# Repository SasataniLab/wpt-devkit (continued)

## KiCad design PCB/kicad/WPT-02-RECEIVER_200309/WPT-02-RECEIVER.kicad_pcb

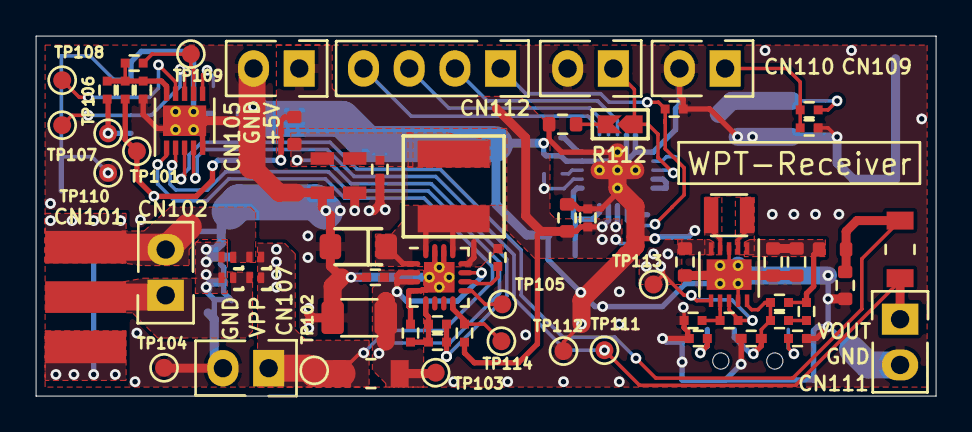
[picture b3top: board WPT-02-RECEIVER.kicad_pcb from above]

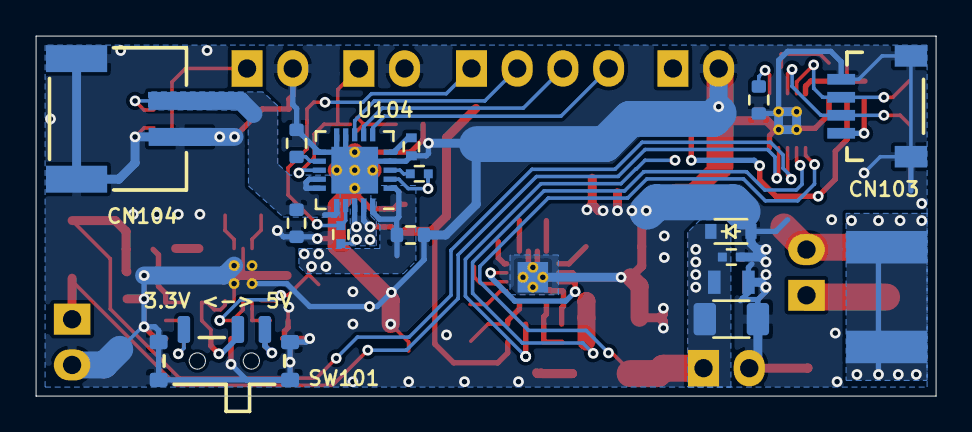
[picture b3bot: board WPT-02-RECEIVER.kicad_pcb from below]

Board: 4 copper layers, 50.0 x 20.0 mm, 84 parts (15 on the bottom side), 40 nets.

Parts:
C101: 0.022u/50(X7R); GRM15
C102, C107: 10u/50(X5R); GRM31
C103, C104, C116, C119: 0.1u/50(X7R); GRM15
C105: 1000p/50(C0G); GRM15
C106: 0.1u/100(X7R); GRM21
C108, C109: 22u/16(X5R); GRM21
C110: 10n/50(X7R); GRM15
C111: 10u/25(X5R); GRM18
C112, C122: 22u/10(X5R); GRM18
C113: 68p/50(C0G); GRM15
C117, C118, C120: 4.7u/16(X5R); GRM18
C123: OPEN; GRM18
CN101: CON-SMA-EDGE-S
CN102, CN105, CN107, CN109, CN110, CN111: ULO-PH409-1*2SF11; ULO-PH409-1x2SX1
CN103: SM04B-SRSS-TB(LF)(SN); SM04B-SRSS-TB
CN104: S2B-PH-SM4-TB(LF)(SN); S2B-PH-SM4-TB
CN112: ULO-PH409-1*4SF11; ULO-PH409-1x4SX1
D101, D102, D105, D106: PMEG6010AESBYL; SOD-993_Nexperia
D103: S210FA; SOD-123FA_OnSemi
D104: MM3Z39VT1G; SOD-323
FB101, FB102: BLM18PG330SN1D; BLM18
L101: NR5040T4R7N; NR5040
L102: DFE252012P-3R3M=P2; DFE252012C
R101: 82kF; R_0402
R102: 18kF; R_0402
R103, R107: 27mF(1/4W); R_1206
R104, R116: 10kF; R_0402
R105, R106, R108, R114, R119: OPEN; R_0402
R109: 750kF; R_0402
R110: 91kF; R_0402
R111: 820kF; R_0402
R112: SHORT_JUMPER; JP_SMD
R113, R115: 0; R_0402
R117: 0; R_0603
R118: NCP15XH103F03RC; NTC_0402
R120, R126: 100kF; R_0402
R121: 143kF; R_0402
R123: 100kF; R_0603
R124: 10kF; R_0603
SW101: CUS-12TB
TP101, TP102, TP103, TP104, TP105, TP106, TP107, TP108, TP109, TP110, TP111, TP112, TP113, TP114: TP1.0; TP_1mm
U101: TS30042-M000QFNR; QFN-16-1EP_3x3mm_Pitch0.5mm_Semtech
U102: MP2155GQ-Z; DFN-10-1EP_3x3mm_Pitch0.5mm_MPS
U103: PAC1720-1-AIA-TR; DFN-10-1EP_3x3mm_Pitch0.5mm_microchip_9Q
U104: MCP73871T-1CCI_ML; QFN-20-1EP_4x4mm_Pitch0.5mm_microchip_ML
VD101: CG0402MLC-3.3LG; CG0402

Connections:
+5V: C118.1, C119.1, CN105.1, FB101.2, R104.2, R114.2, R119.2, R120.2, TP101.1, U104.2, U104.18, U104.19
/CHG_EN: CN112.1, R119.1, R126.2, U104.17
/CHG_STAT1: CN112.2, U104.8
/CHG_STAT2: CN112.3, U104.7
/PWRGD_5V: R104.1, TP114.1, U101.8
/SCL: CN103.3, TP108.1, U103.9
/SDA: CN103.2, TP107.1, U103.8
/VEXT: CN103.1, R115.1, TP106.1
/VOUT: CN111.1, R107.1, TP111.1, U103.4
/~ALERT: R116.1, TP109.1, U103.7
/~CHG_PG: CN112.4, U104.6
GND: C102.2, C103.2, C104.2, C105.2, C106.2, C107.2, C108.2, C109.2, C111.2, C112.2, C116.2, C117.2, C118.2, C119.2, C120.2, C122.2, C123.2, CN103.4, CN103.FG, CN104.2, CN104.FG, CN105.2, CN107.2, CN109.2, CN110.2, CN111.2, D103.2, D104.2, D105.2, D106.2, R102.1, R106.1, R110.1, R113.1, R117.1, R118.1, R121.1, R123.1, R124.1, R126.1, SW101.FG, TP104.1, TP110.1, TP112.1, U101.4, U101.14, U101.15, U101.17, U102.3, U102.9, U102.11, U103.5, U103.11, U104.4, U104.9, U104.10, U104.11, U104.21, VD101.1
unnamed: C101.1, U101.10
unnamed: C101.2, D103.1, L101.1, U101.1, U101.12, U101.13, U101.16
unnamed: C102.1, C103.1, R103.1, TP103.1, U101.2, U101.3, U101.11, U103.2
unnamed: C104.1, C108.1, C109.1, C110.1, FB101.1, L101.2, R101.2
unnamed: C110.2, R101.1, R102.2, U101.5
unnamed: C112.1, C122.1, FB102.1, R109.2, R111.2, U102.1
unnamed: C113.1, R109.1
unnamed: C113.2, R111.1, SW101.2, U102.10, VD101.2
unnamed: C116.1, R114.1, R115.2, R116.2, U103.10
unnamed: C120.1, CN104.1, R105.2, U104.14, U104.15, U104.16
unnamed: C123.1, FB102.2, R107.2, U103.3
unnamed: CN101.1, CN102.1, D101.2, D105.1
unnamed: CN101.2, CN102.2, D102.2, D106.1
unnamed: CN109.1, R105.1, R106.2
unnamed: CN110.1, R112.2, U104.13
unnamed: L102.1, U102.4
unnamed: L102.2, U102.2
unnamed: R108.1, R113.2, U102.7
unnamed: R110.2, SW101.3
unnamed: R112.1, R124.2
unnamed: R117.2, U103.6
unnamed: R118.2, U104.5
unnamed: R120.1, U104.3
unnamed: R121.2, SW101.1
unnamed: R123.2, U104.12
unnamed: TP105.1, U101.9
VCC: C111.1, C117.1, R108.2, TP113.1, U102.5, U102.6, U102.8, U104.1, U104.20
VPP: C105.1, C106.1, C107.1, CN107.1, D101.1, D102.1, D104.1, R103.2, TP102.1, U103.1

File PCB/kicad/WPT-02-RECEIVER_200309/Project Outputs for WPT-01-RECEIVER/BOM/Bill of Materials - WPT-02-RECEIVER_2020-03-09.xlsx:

Source: | E:\Dropbox\dev\prj\commissioned\University of Tokyo\WPT\electric\kicad\WPT-02-R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
Date: | 09/03/2020 07:57:30
Tool: | Eeschema (5.1.5)-3
Generator: | E:\Dropbox\dev\prj\kicad-library/bom_csv_grouped_by_value_with_fp.py
Component Count: | 84
Mount | Comment | Description | Designator | Footprint | Manufacturer | Manufacturer Part Number | Qnty | Qty for 25Units | Retailer
Yes | 0.022u/50(X7R) | CAP CER 0.022UF 50V X7R 0402 | C101, | murata:GRM15 | Murata Electronics | GRM155R71H223KA12D | 1 | 25
Yes | 10u/50(X5R) | CAP CER 10UF 50V X5R 1206 | C102, C107, | murata:GRM31 | Samsung Electro-Mechanics | CL31A106KBHNNNE | 2 | 50
Yes | 0.1u/50(X7R) | CAP CER 0.1UF 50V X7R 0402 | C103, C104, C116, C119, | murata:GRM15 | Murata Electronics | GCM155R71H104KE02D | 4 | 100
Yes | 1000p/50(C0G) | CAP CER 1000PF 50V 5% NP0 0402 | C105, | murata:GRM15 | Murata Electronics | GRM1555C1H102JA01D | 1 | 25
Yes | 0.1u/100(X7R) | CAP CER 0.1UF 100V X7R 0805 | C106, | murata:GRM21 | Murata Electronics | GCM21BR72A104KA37L | 1 | 25
Yes | 22u/16(X5R) | CAP CER 22UF 16V X5R 0805 | C108, C109, | murata:GRM21 | Samsung Electro-Mechanics | CL21A226MOCLRNC | 2 | 50
Yes | 10n/50(X7R) | CAP CER 10000PF 50V X7R 0402 | C110, | murata:GRM15 | Yageo | CC0402KRX7R9BB103 | 1 | 25
Yes | 10u/25(X5R) | CAP CER 10UF 25V 20% X5R 0603 | C111, | murata:GRM18 | Murata Electronics | GRM188R61E106MA73D | 1 | 25
Yes | 22u/10(X5R) | CAP CER 22UF 10V X5R 0603 | C112, C122, | murata:GRM18 | Murata Electronics | GRM188R61A226ME15D | 2 | 50
Yes | 68p/50(C0G) | CAP CER 68PF 50V C0G/NP0 0402 | C113, | murata:GRM15 | Murata Electronics | GCM1555C1H680JA16D | 1 | 25
Yes | 4.7u/16(X5R) | CAP CER 4.7UF 16V X5R 0603 | C117, C118, C120, | murata:GRM18 | Murata Electronics | GRM188R61C475KAAJD | 3 | 75
No | OPEN |  | C123, | murata:GRM18 |  |  | 1 | 25
No | CON-SMA-EDGE-S | CONN SMA JACK STR EDGE MNT | CN101, | RF_Solutions:CON-SMA-EDGE-S | RF Solutions | CON-SMA-EDGE-S | 1 | 25
No | ULO-PH409-1*2SF11 | CON HEADER 2 PIN THROUGHTHOLE 6.1/2.5/3mm HEIGHT | CN102, CN105, CN107, CN109, CN110, CN111, | ulo:ULO-PH409-1x2SX1 | ULO Electronic | ULO-PH409-1x2SX1 | 6 | 150
Yes | SM04B-SRSS-TB(LF)(SN) | CONN HEADER SH 4POS SIDE 1MM TIN | CN103, | Connectors_JST:SM04B-SRSS-TB | JST | SM04B-SRSS-TB(LF)(SN) | 1 | 25
Yes | S2B-PH-SM4-TB(LF)(SN) | CONN HEADER PH SIDE 2POS 2MM SMD | CN104, | Connectors_JST:S2B-PH-SM4-TB | JST | S2B-PH-SM4-TB(LF)(SN) | 1 | 25
No | ULO-PH409-1*4SF11 | CON HEADER 4 PIN THROUGHTHOLE 6.1/2.5/3mm HEIGHT | CN112, | ulo:ULO-PH409-1x4SX1 | ULO Electric | ULO-PH409-1*4SF11 | 1 | 25
Yes | PMEG6010AESBYL | DIODE SCHOTTKY 60V 1A DSN1006-2 | D101, D102, D105, D106, | Diodes_SMD:SOD-993_Nexperia | Nexperia | PMEG6010AESBYL | 4 | 100
Yes | S210FA | DIODE SCHOTTKY 100V 2A SOD123FA | D103, | Diodes_SMD:SOD-123FA_OnSemi | ON Semiconductor | S210FA | 1 | 25
Yes | MM3Z39VT1G | DIODE ZENER 39V 300MW SOD323 | D104, | Diodes_SMD:SOD-323 | ON Semiconductor | MM3Z39VT1G | 1 | 25
Yes | BLM18PG330SN1D | FERRITE CHIP 33 OHM 3000MA 0603 | FB101, FB102, | murata:BLM18 | Murata Electronics | BLM18PG330SN1D | 2 | 50
Yes | NR5040T4R7N | FIXED IND 4.7UH 3.1A 37.7 MOHM | L101, | taiyo-yuden:NR5040 | Taiyo Yuden | NR5040T4R7N | 1 | 25
Yes | DFE252012P-3R3M=P2 | FIXED IND 3.3UH 2.3A 140 MOHM | L102, | murata:DFE252012C | Murata Electronics | DFE252012P | 1 | 25
Yes | 82kF | RES SMD 82K OHM 1% 1/16W 0402 | R101, | yageo:R_0402 | Yageo | RC0402FR-0782KL | 1 | 25
Yes | 18kF | RES SMD 18K OHM 5% 1/16W 0402 | R102, | yageo:R_0402 | Yageo | RC0402FR-0718KL | 1 | 25
Yes | 27mF(1/4W) | RES 0.027 OHM 1% 1/4W 1206 3216Metric | R103, R107, | yageo:R_1206 | Yageo | RL1206FR-070R027L | 2 | 50
Yes | 10kF | RES SMD 10K OHM 1% 1/16W 0402 | R104, R116, | yageo:R_0402 | Yageo | RC0402FR-0710KL | 2 | 50
No | OPEN |  | R105, R106, R108, R114, R119, | yageo:R_0402 |  |  | 5 | 125
Yes | 750kF | RES SMD 750K OHM 1% 1/16W 0402 | R109, | yageo:R_0402 | Yageo | RC0402FR-07750KL | 1 | 25
Yes | 91kF | RES SMD 91K OHM 1% 1/16W 0402 | R110, | yageo:R_0402 | Yageo | RC0402FR-0791KL | 1 | 25
Yes | 820kF | RES SMD 820K OHM 1% 1/16W 0402 | R111, | yageo:R_0402 | Yageo | RC0402FR-07820KL | 1 | 25
Yes | 0 | RES SMD 0.0OHM JUMPER 1/16W 0402 | R113, R115, | yageo:R_0402 | Yageo | RC0402FR-070RL | 2 | 50
Yes | 0 | RES SMD 0.0OHM JUMPER 1/10W 0603 | R112, R117, | yageo:R_0603 | Yageo | RC0603FR-070RL | 2 | 50
Yes | NCP15XH103F03RC | THERMISTOR 10K OHM NTC 0402 SMD | R118, | murata:NTC_0402 | Murata Electronics | NCP15XH103F03RC | 1 | 25
Yes | 100kF | RES SMD 100K OHM 1% 1/16W 0402 | R120, R126, | yageo:R_0402 | Yageo | RC0402FR-07100KL | 2 | 50
Yes | 143kF | RES SMD 143K OHM 1% 1/16W 0402 | R121, | yageo:R_0402 | Yageo | RC0402FR-07143KL | 1 | 25
Yes | 100kF | RES SMD 100K OHM 1% 1/10W 0603 | R123, | yageo:R_0603 | Yageo | RC0603FR-07100KL | 1 | 25
Yes | 10kF | RES SMD 10K OHM 1% 1/10W 0603 | R124, | yageo:R_0603 | Yageo | RC0603FR-0710KL | 1 | 25
Yes | CUS-12TB | SWITCH SLIDE SPDT 300MA 4V | SW101, | Nidec_Copal_Electronics:CUS-12TB | Nidec Copal Electronics | CUS-12TB | 1 | 25
No | TP1.0 | TEST POINT 1mm | TP101, TP102, TP103, TP104, TP105, TP106, TP107, TP108, TP109, TP110, TP111, TP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 | TestPoint:TP_1mm |  |  | 14 | 350
Yes | TS30042-M000QFNR | IC REG BUCK ADJ 2A SYNC 16-VQFN | U101, | Housings_DFN_QFN:QFN-16-1EP_3x3mm_Pitch0.5mm_Semtech | Semtech | TS30042-M000QFNR | 1 | 25
Yes | MP2155GQ-Z | IC REG BCK BST 3.3V/ADJ 10QFN | U102, | Housings_DFN_QFN:DFN-10-1EP_3x3mm_Pitch0.5mm_MPS | Monolithic Power Systems Inc. | MP2155GQ-Z | 1 | 25
Yes | PAC1720-1-AIA-TR | IC CURRENT SENSE MON DUAL 10VDFN | U103, | Housings_DFN_QFN:DFN-10-1EP_3x3mm_Pitch0.5mm_microchip_9Q | microchip | PAC1720-1-AIA-TR | 1 | 25
Yes | MCP73871T-1CCI_ML | USB/AC BATTERY CHARGER 4.1V 6H Timer 3.1V LBO | U104, | Housings_DFN_QFN:QFN-20-1EP_4x4mm_Pitch0.5mm_microchip_ML | microchip | MCP73871T-1CCI/ML | 1 | 25
Yes | CG0402MLC-3.3LG | VARISTOR 3.3V 0402 | VD101, | bourns:CG0402 | Bourns Inc. | CG0402MLC-3.3LG | 1 | 25

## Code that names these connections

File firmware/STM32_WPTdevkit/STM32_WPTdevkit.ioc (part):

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Mcu.Name=STM32G474R(B-C-E)Tx
Mcu.Package=LQFP64
Mcu.UserName=STM32G474RETx
PA0.GPIOParameters=GPIO_Label
PA0.GPIO_Label=ADC1_IN1_VDC
PA0.Mode=IN1-Single-Ended
PA0.Signal=ADC1_IN1
PA1.GPIOParameters=GPIO_Label
PA1.GPIO_Label=NC_PA1
PA1.Mode=INP
PA1.Signal=COMP1_INP
PA11.Mode=Device
PA11.Signal=USB_DM
PA12.Mode=Device
PA12.Signal=USB_DP
PA13.Mode=Serial_Wire
PA13.Signal=SYS_JTMS-SWDIO
PA14.Mode=Serial_Wire
PA14.Signal=SYS_JTCK-SWCLK
PA2.GPIOParameters=GPIO_Label
PA2.GPIO_Label=GPIO_DISP_CS
PA2.Signal=GPIO_Output
PA3.GPIOParameters=GPIO_Label
PA3.GPIO_Label=GPIO_DISP_DC
PA3.Signal=GPIO_Output
PA4.GPIOParameters=GPIO_Label
PA4.GPIO_Label=GPIO_DISP_RST
PA4.Signal=GPIO_Output
PA5.GPIOParameters=GPIO_Label
PA5.GPIO_Label=SPI1_CLK_DISP
PA5.Mode=Full_Duplex_Master
PA5.Signal=SPI1_SCK
PA6.GPIOParameters=GPIO_Label
PA6.GPIO_Label=SPI1_MISO_DISP
PA6.Mode=Full_Duplex_Master
PA6.Signal=SPI1_MISO
PA7.GPIOParameters=GPIO_Label
PA7.GPIO_Label=SPI1_MOSI_DISP
PA7.Mode=Full_Duplex_Master
PA7.Signal=SPI1_MOSI
PB0.GPIOParameters=GPIO_Label
PB0.GPIO_Label=GPIO_HVDCDC_EN
PB0.Signal=GPIO_Output
PB10.GPIOParameters=GPIO_Label
PB10.GPIO_Label=HRTIM1_FLT3_OCP
PB10.Mode=Fault_Enable3
PB10.Signal=HRTIM1_FLT3
PB11.GPIOParameters=GPIO_Label
PB11.GPIO_Label=ZVS_VTH_DAC
PB11.Signal=GPIO_Analog
PB12.GPIOParameters=GPIO_Label
PB12.GPIO_Label=HRTIM1_CHC1_H_SIG1
PB12.Mode=Output_TC1TC2
PB12.Signal=HRTIM1_CHC1
PB13.GPIOParameters=GPIO_Label
PB13.GPIO_Label=HRTIM1_CHC2_L_SIG1
PB13.Mode=Output_TC1TC2
PB13.Signal=HRTIM1_CHC2
PB14.GPIOParameters=GPIO_Label
PB14.GPIO_Label=HRTIM1_CHD1_L_SIG2
PB14.Mode=Output_TD1TD2
PB14.Signal=HRTIM1_CHD1
PB15.GPIOParameters=GPIO_Label
PB15.GPIO_Label=HRTIM1_CHD2_H_SIG2
PB15.Mode=Output_TD1TD2
PB15.Signal=HRTIM1_CHD2
PB2.GPIOParameters=GPIO_PuPd,GPIO_Label
PB2.GPIO_Label=GPIO_N_ALERT
PB2.GPIO_PuPd=GPIO_PULLUP
PB2.Signal=GPIO_Input
PB3.GPIOParameters=GPIO_Label
PB3.GPIO_Label=GPIO_SW_MISC1
PB3.Signal=GPIO_Input
PB4.GPIOParameters=GPIO_Label
PB4.GPIO_Label=GPIO_SW_MISC2
PB4.Signal=GPIO_Input
PC1.GPIOParameters=GPIO_Label
PC1.GPIO_Label=NC_PC1
PC1.Mode=INP
PC1.Signal=COMP3_INP
PC10.GPIOParameters=GPIO_Label
PC10.GPIO_Label=GPIO_VUSB_SENSE
PC10.Signal=GPIO_Input
PC11.GPIOParameters=GPIO_Label
PC11.GPIO_Label=HRTIM1_EEV2_ZVS_A
PC11.Mode=External_Evt_enable2
PC11.Signal=HRTIM1_EEV2
PC12.GPIOParameters=GPIO_Label
PC12.GPIO_Label=HRTIM1_EEV1_ZVS_B
PC12.Mode=External_Evt_enable1
PC12.Signal=HRTIM1_EEV1
PC13.GPIOParameters=GPIO_Label
PC13.GPIO_Label=GPIO_ENCODER_PUSH
PC13.Signal=GPIO_Input
PC2.GPIOParameters=GPIO_Label
PC2.GPIO_Label=ADC2_IN8_EXTERNAL
PC2.Mode=IN8-Single-Ended
PC2.Signal=ADC2_IN8
PC4.GPIOParameters=GPIO_Label
PC4.GPIO_Label=USART1_TX_EXTERNAL
PC4.Mode=Asynchronous
PC4.Signal=USART1_TX
PC5.GPIOParameters=GPIO_Label
PC5.GPIO_Label=USART1_RX_EXTERNAL
PC5.Mode=Asynchronous
PC5.Signal=USART1_RX
PC6.GPIOParameters=GPIO_Label
PC6.GPIO_Label=TIM3_CH1_ENCODER
PC6.Signal=S_TIM3_CH1
PC7.GPIOParameters=GPIO_Label
PC7.GPIO_Label=TIM3_CH2_ENCODER
PC7.Signal=S_TIM3_CH2
PC8.GPIOParameters=GPIO_Label
PC8.GPIO_Label=I2C3_SCL_CTRL
PC8.Mode=I2C
PC8.Signal=I2C3_SCL
PC9.GPIOParameters=GPIO_Label
PC9.GPIO_Label=I2C3_SDA_CTRL
PC9.Mode=I2C
PC9.Signal=I2C3_SDA
PF0-OSC_IN.Mode=HSE-External-Oscillator
PF0-OSC_IN.Signal=RCC_OSC_IN
PF1-OSC_OUT.Mode=HSE-External-Oscillator
PF1-OSC_OUT.Signal=RCC_OSC_OUT
RCC.HSE_VALUE=24000000
RCC.SYSCLKFreq_VALUE=169500000
RCC.SYSCLKSource=RCC_SYSCLKSOURCE_PLLCLK
board=custom

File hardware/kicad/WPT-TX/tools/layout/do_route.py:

#!/usr/bin/env python3
"""Routing driver: DRC -> unconnected pairs -> A* -> save, repeated. usage: do_route.py BOARD [max_iters]"""
import collections, math, re, sys, time
import router as R

PLANE = {'GND', '+3V3'}
path = sys.argv[1] if len(sys.argv) > 1 else ''
iters = int(sys.argv[2]) if len(sys.argv) > 2 and sys.argv[2].isdigit() else 4


def prio(net):
    if net == 'Net-(U301-A)':
        return -1
    if net in ('Net-(U2-PF0)', 'Net-(U2-PF1)', 'Net-(U2-VDDA)') or net in PLANE:
        return 0
    if 'USB' in net or 'VBUS' in net or 'CC' in net:
        return 1
    if any(k in net for k in ('HRTIM1_CH', '_Sig', 'OutA', 'OutB', 'VSW')):
        return 2
    return 3


def manual(r):
    """Hand-placed pieces the grid router should not improvise (kept as fixed copper)."""
    r._fixed = True
    T = lambda net, pts, w=0.2: [r.add_track(net, 'F.Cu', a, b, w) for a, b in zip(pts, pts[1:])]
    # +5V for the relocated level shifter: via onto the In2 +5V link
    r.add_via('+5V', (162.2, 164.2))
    # USB-C: join the two D+ pads below the pad row and the two D- pads above it (under the shell)
    T('/USB_D_P', [(193.05, 142.6), (193.05, 143.35), (194.05, 143.35), (194.05, 142.6)])
    T('/USB_D_N', [(193.55, 142.1), (193.55, 141.35), (194.55, 141.35), (194.55, 142.1)])
    # connector -> ESD array
    T('/USB_D_P', [(193.05, 143.35), (193.05, 143.55), (192.75, 143.85), (191.7, 143.85), (191.35, 144.2), (191.35, 144.5)])
    T('/USB_D_N', [(194.55, 142.6), (194.55, 143.75), (194.05, 144.25), (193.4, 144.25)])
    # ESD array -> MCU: out of the south side, along the south strip, up the east side, straddling the ESD ground pin
    T('/USB_D_P', [(186.65, 160.1), (186.65, 162.3), (187.05, 162.7), (191.6, 162.7), (192.0, 162.3), (192.0, 151.5),
                   (191.35, 150.85), (191.35, 147.4)], 0.3)
    T('/USB_D_N', [(186.15, 160.1), (186.15, 162.7), (186.65, 163.2), (192.0, 163.2), (192.5, 162.7), (192.5, 151.5),
                   (193.25, 150.75), (193.25, 147.4)], 0.3)
    # ESD array ground pin and VBUS pin drop straight to vias
    T('GND', [(192.3, 147.4), (192.3, 148.9)], 0.25)
    r.add_via('GND', (192.3, 148.9))
    T('/VBUS', [(192.3, 145.1), (192.3, 145.95)], 0.25)
    r.add_via('/VBUS', (192.3, 145.95))
    # the ESD array is flow-through: its two pins per line are joined under the body
    T('/USB_D_P', [(191.35, 144.86), (191.35, 147.14)], 0.3)
    T('/USB_D_N', [(193.25, 144.86), (193.25, 147.14)], 0.3)
    # the two VBUS pad groups are joined under the connector shell; one via on the board side of the east group
    T('/VBUS', [(191.55, 142.2), (191.55, 140.6), (196.05, 140.6), (196.05, 142.2)])
    T('/VBUS', [(196.2, 142.6), (196.2, 143.9)], 0.25)
    r.add_via('/VBUS', (196.2, 143.9))
    # VBUS: back-side link to the ESD array, front-side run to the sense divider; divider mid-point link
    for a_, b_ in zip([(192.3, 145.95), (192.9, 145.35), (194.75, 145.35), (196.2, 143.9)], [(192.9, 145.35), (194.75, 145.35), (196.2, 143.9)]):
        r.add_track('/VBUS', 'B.Cu', a_, b_, 0.25)
    T('/VBUS', [(196.2, 143.9), (196.2, 144.6), (197.2, 145.6), (197.6, 146.0), (197.6, 146.4)], 0.25)
    T('/GPIO_VUSB_SENSE', [(197.6, 147.51), (197.6, 148.49)], 0.25)
    # CC lines to their 5.1k resistors
    T('Net-(J5-CC1)', [(195.05, 142.6), (195.05, 143.55), (195.3, 143.8), (195.3, 144.1)])
    T('Net-(J5-CC2)', [(192.05, 142.6), (192.05, 143.15), (191.85, 143.35), (190.9, 143.35), (190.3, 143.95), (190.3, 144.4)])
    r._fixed = False


def rip(path, r, nets):
    """Remove the copper this router added for the given nets and reload."""
    keys = set(k for n in nets for k in r.reg.get(n, []))
    b = r.board
    MMX = 1e6
    n = 0
    for t in list(b.GetTracks()):
        net = t.GetNetname()
        if net not in nets:
            continue
        if t.GetClass() == 'PCB_VIA':
            k = r.vkey(net, (t.GetPosition().x / MMX, t.GetPosition().y / MMX))
        else:
            k = r.tkey(net, b.GetLayerName(t.GetLayer()), (t.GetStart().x / MMX, t.GetStart().y / MMX), (t.GetEnd().x / MMX, t.GetEnd().y / MMX))
        if k in keys:
            b.Remove(t)
            n += 1
    for net in nets:
        r.reg.pop(net, None)
    r.save()
    return R.Router(path, reg=r.reg, protected=r.protected)


INNER = '--inner' in sys.argv
if '--no-corridors' in sys.argv:
    R.DEFAULT_CORRIDORS = ()
PLANES_ONLY = '--planes-only' in sys.argv
FAST = ('HRTIM1_CH', '_Sig', 'USB_D', 'U2-PF', 'VSWA_SENSE', 'VSWB_SENSE', 'OutA', 'OutB', 'U301-A', 'VBUS', 'CC')


def slow(net):
    """Nets that may borrow the inner power layer (as the legacy board already does)."""
    return INNER and not any(k in net for k in FAST) and net not in PLANE


def attempt(r, net, A, B, **kw):
    kw.setdefault('inner', slow(net))
    for margin in (4.0, 10.0, 30.0):
        if r.route(net, A, B, margin=margin, max_nodes=6_000_000, **kw):
            return True
    return False


def main():
    global REG, PROT
    if '--manual' in sys.argv:
        r = R.Router(path)
        manual(r)
        r.save()
    REG, PROT = {}, {'GND', '+3V3', '+5V', '/VBUS', '/USB_D_P', '/USB_D_N', 'Net-(J5-CC1)', 'Net-(J5-CC2)', 'Net-(U2-VDDA)', 'Net-(U2-PF0)', 'Net-(U2-PF1)', 'Net-(U301-A)'}
    RIP_PASSES = int(sys.argv[3]) if len(sys.argv) > 3 and sys.argv[3].isdigit() else 4
    ripcount = collections.Counter()
    for it in range(iters):
        txt = R.run_drc(path, path.replace('.kicad_pcb', f'_drc{it}.rpt'))
        tasks = R.parse_unconnected(txt)
        print(f'--- iteration {it}: {len(tasks)} unconnected')
        if not tasks:
            break
        r = R.Router(path, reg=REG, protected=PROT)
        tasks.sort(key=lambda t: (prio(t[0]['net']), math.dist((t[0]['x'], t[0]['y']), (t[1]['x'], t[1]['y']))))
        done = fail = 0
        failed = []
        t0 = time.time()
        for a, b in tasks:
            net = a['net']
            if PLANES_ONLY and not (net in PLANE or prio(net) <= 0 or net == '+5V'):
                continue
            if 'CN301' in a['desc'] + b['desc']:
                continue          # pre-existing: the SMA pad and the B.Cu track under it were never joined
            A = (a['x'], a['y'], a['layers'])
            B = (b['x'], b['y'], b['layers'])
            d = math.dist(A[:2], B[:2])
            ok = False
            if 'In2.Cu' in a['desc'] or 'In2.Cu' in b['desc'] or 'Zone' in (a['kind'], b['kind']):
                # one side lives on an inner layer / pour: drop a via next to the outer-layer item
                for it2 in (a, b):
                    if 'In2.Cu' in it2['desc'] or it2['kind'] == 'Zone':
                        continue
                    if net == '+5V':
                        ok = attempt(r, net, (it2['x'], it2['y'], it2['layers']), (162.2, 164.2, ['F.Cu', 'B.Cu']))
                    elif len(it2['layers']) == 1:
                        ok = r.stub_via(net, it2['x'], it2['y'], it2['layers'][0])
            elif net in PLANE:
                if d < 4.0:
                    ok = attempt(r, net, A, B, via_cost=0.6)
                if not ok:
                    for it2 in (a, b):
                        if it2['kind'] == 'Pad' and len(it2['layers']) == 1:
                            ok = r.stub_via(net, it2['x'], it2['y'], it2['layers'][0]) or ok
            else:
                ok = attempt(r, net, A, B)
                if not ok and it < RIP_PASSES:
                    hit = r.route(net, A, B, margin=30.0, max_nodes=6_000_000, soft=True, inner=slow(net))
                    if hit is not False and hit:
                        hit = {h for h in hit if ripcount[h] < 2 and h not in PROT}
                        if hit:
                            for h in hit:
                                ripcount[h] += 1
                            r = rip(path, r, hit)
                            ok = attempt(r, net, A, B)
                            print(f'   rip-up for {net.split("/")[-1]}: {sorted(h.split("/")[-1] for h in hit)} -> {"ok" if ok else "still failing"}')
                            if ok:
                                PROT.add(net)
            if ok:
                done += 1
            else:
                fail += 1
                failed.append((net, round(d, 1), a['desc'][:40], b['desc'][:40]))
        r.save()
        print(f'routed {done}, failed {fail}, {time.time() - t0:.0f} s')
        for f in failed[:40]:
            print('   FAIL', f)
    txt = R.run_drc(path, path.replace('.kicad_pcb', '_drc_final.rpt'))
    blocks = re.split(r'\n(?=\[)', txt)
    c = collections.Counter(b.split(']')[0][1:] for b in blocks if b.startswith('['))
    print({k: v for k, v in c.items() if k not in ('silk_overlap', 'silk_over_copper', 'lib_footprint_issues', 'silk_edge_clearance')})


if __name__ == '__main__':
    main()

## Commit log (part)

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2022-04-05 Create wpt_toolkit_TX.ino
    init commit
2022-04-05 changed filename
2022-04-05 copied sleep
    https://www.hiramine.com/physicalcomputing/atmega328/sleepbuttonwakeup.html
2022-04-06 comment out sleep
2022-04-06 added pcb schmatic pdf
2022-04-06 hoge
2022-04-14 added pcb files
2023-10-30 add arduino file for mode switching
2024-07-09 Add initial firmware
2024-07-19 draft scpi interface and working
2024-07-19 add initial command reference
2024-07-19 Add power on/off commands
2024-07-19 organize dir
2024-07-20 update command reference
2024-07-20 updated fw commands
2024-07-22 Create LICENSE
2024-08-02 add gitignore
2024-08-02 make arduino firmware a installable package
2024-08-02 moved command reference
2024-08-02 add some docs
2024-08-02 add notes on dependencies
